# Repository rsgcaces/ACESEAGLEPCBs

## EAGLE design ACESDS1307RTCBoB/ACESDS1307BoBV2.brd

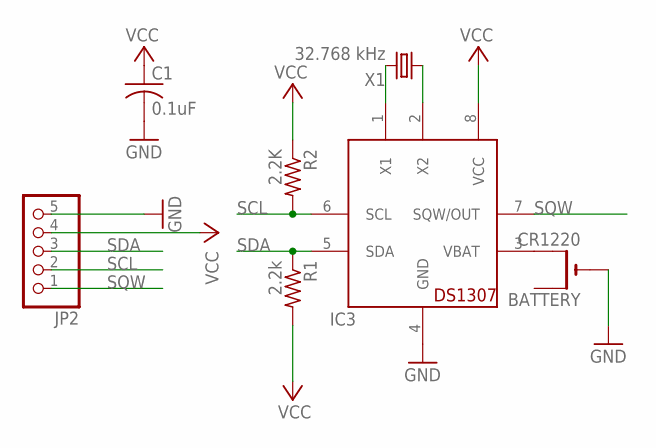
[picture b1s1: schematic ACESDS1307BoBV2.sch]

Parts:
BATTERY: CR1220; CR1220-THM
C1: 0.1uF; C025-025X050
IC3: DS1307; DIL08
JP2: PINHD-1X5; 1X05
R1: 2.2k; 0207/10
R2: 2.2K; 0207/10
X1: 32.768 kHz; TC38H

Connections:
GND: BATTERY.-, C1.2, IC3.4 (GND), JP2.5
unnamed: IC3.1 (X1), X1.2
unnamed: IC3.2 (X2), X1.1
unnamed: BATTERY.+2 (+1), IC3.3 (VBAT)
SCL: IC3.6 (SCL), JP2.2, R2.2
SDA: IC3.5 (SDA), JP2.3, R1.1
SQW: IC3.7 (SQW/OUT), JP2.1
VCC: C1.1, IC3.8 (VCC), JP2.4, R1.2, R2.1

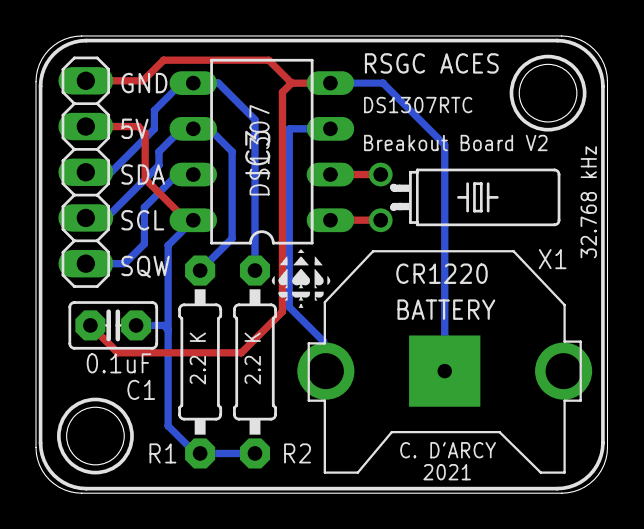
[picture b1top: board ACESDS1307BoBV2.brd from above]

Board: 2 copper layers, 31.8 x 25.4 mm, 9 parts (0 on the bottom side), 8 nets.

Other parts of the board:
U$1: MEDIUM_BSILK_TEXT
U$2: SMALL_TSILK

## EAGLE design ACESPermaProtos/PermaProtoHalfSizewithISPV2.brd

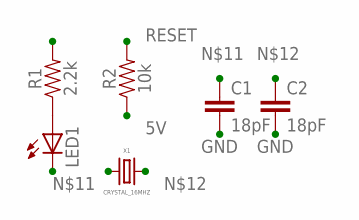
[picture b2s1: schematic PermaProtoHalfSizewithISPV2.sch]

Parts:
C1, C2: 18pF; 0603
LED1: LEDCHIP-LED0603; CHIP-LED0603
R1: 2.2k; 0603
R2: 10k; 0603
X1: CRYSTAL_16MHZ; HC49US

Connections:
5V: R2.1
GND: C1.2, C2.2, LED1.C
unnamed: C1.1, X1.1
unnamed: C2.1, X1.2
unnamed: LED1.A, R1.1
RESET: R2.2
SCK: R1.2

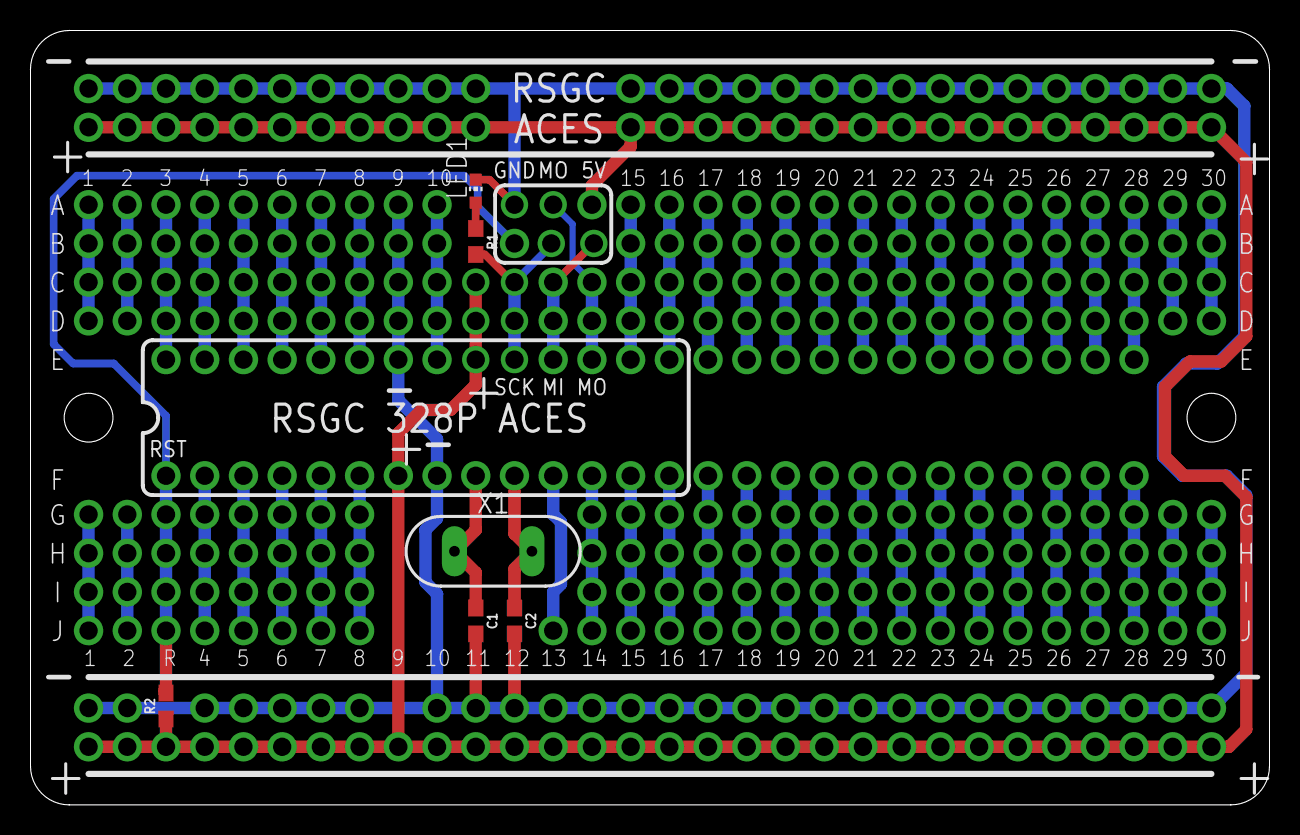
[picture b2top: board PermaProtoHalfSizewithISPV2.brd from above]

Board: 2 copper layers, 81.3 x 50.8 mm, 10 parts (0 on the bottom side), 4 nets.

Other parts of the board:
U$1, U$2: SMALL_TSILK_TEXT
U$3, U$4: SMALL_BSILK_TEXT

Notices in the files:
parts and their libraries:
SparkFun-Resistors: Licensing: Creative Commons ShareAlike 4.0 International - https://creativecommons.org/licenses/by-sa/4.0
